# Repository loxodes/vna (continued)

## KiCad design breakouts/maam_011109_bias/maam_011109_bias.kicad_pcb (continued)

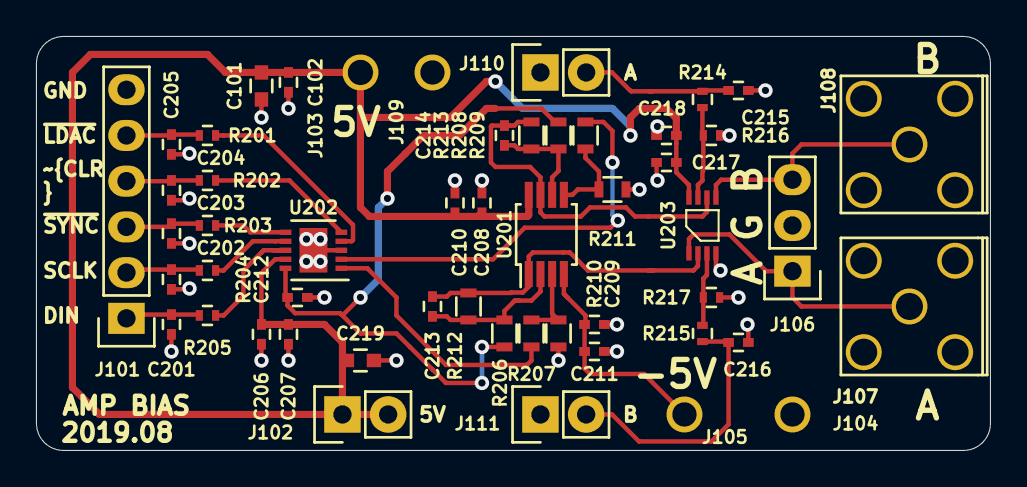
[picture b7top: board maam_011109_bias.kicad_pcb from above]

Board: 2 copper layers, 53.0 x 23.0 mm, 52 parts (0 on the bottom side), 28 nets.

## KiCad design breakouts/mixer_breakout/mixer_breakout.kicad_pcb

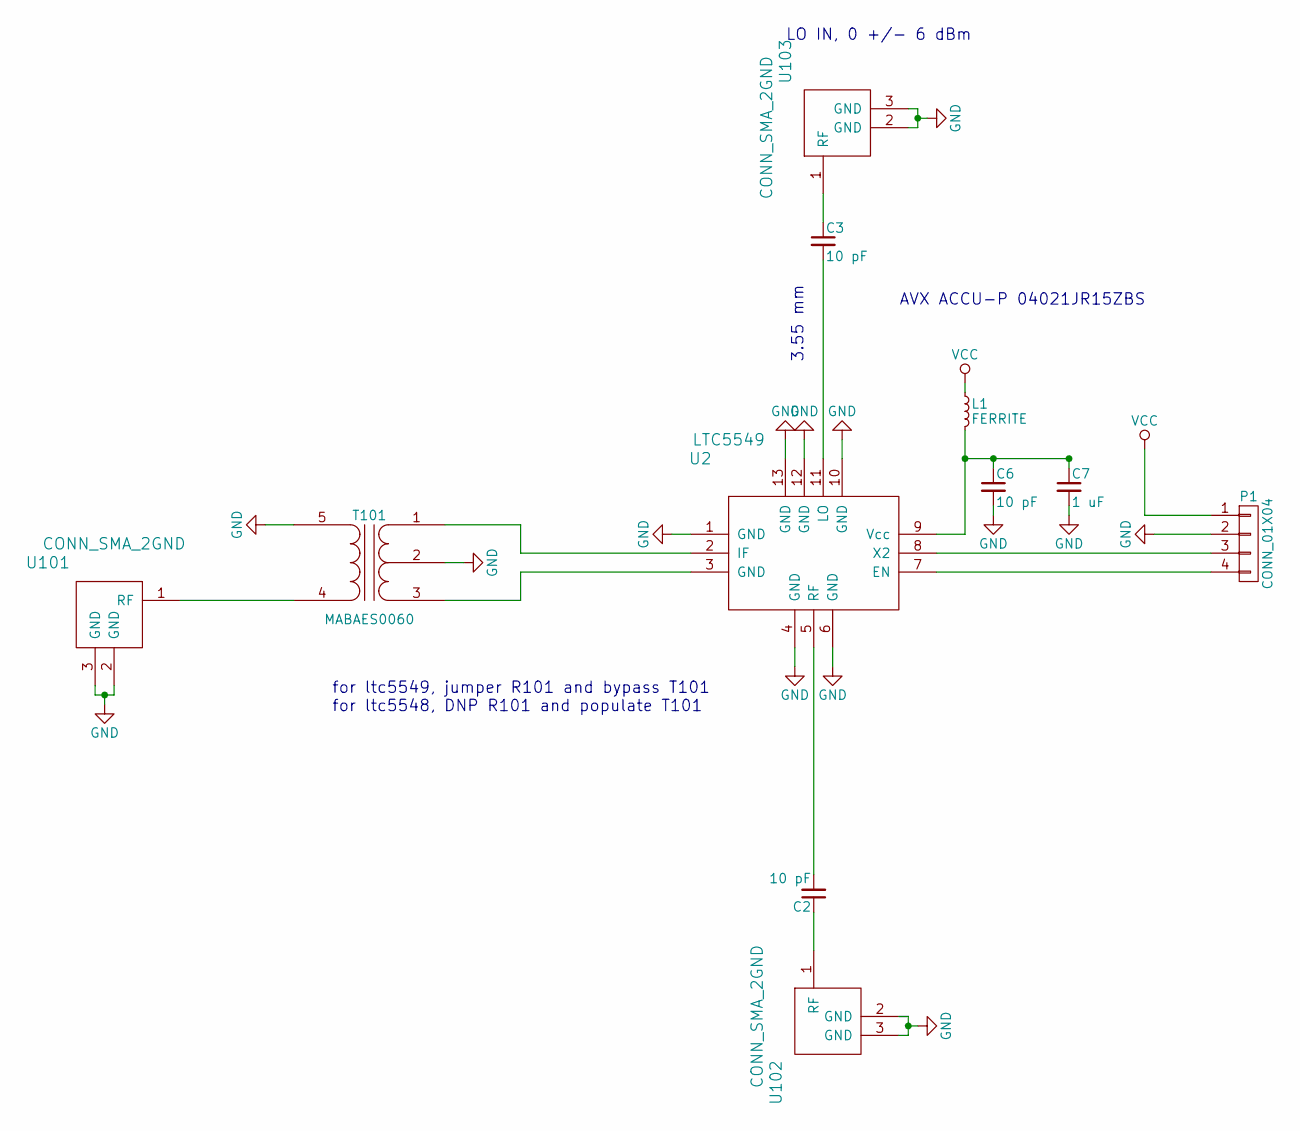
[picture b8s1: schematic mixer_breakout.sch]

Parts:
C2, C3: 10 pF; C_0402
C6: 10 pF; C_0603
C7: 1 uF; C_0603
L1: FERRITE; C_0603
P1: CONN_01X04; Pin_Header_Straight_1x04
T101: MABAES0060; 5LEAD_BALUN_4p83mm_3p3mm
U2: LTC5549; QFN_12_3mm2mm
U101, U102, U103: CONN_SMA_2GND; 142-0721-882_sma_cutout

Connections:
GND: C6.2, C7.2, P1.2, T101.2 (PM), T101.5 (S2), U2.1 (GND), U2.4 (GND), U2.6 (GND), U2.10 (GND), U2.12 (GND), U2.13 (GND), U101.2 (GND), U101.3 (GND), U102.2 (GND), U102.3 (GND), U103.2 (GND), U103.3 (GND)
unnamed: C2.1, U102.1 (RF)
unnamed: C2.2, U2.5 (RF)
unnamed: C3.1, U103.1 (RF)
unnamed: C3.2, U2.11 (LO)
unnamed: C6.1, C7.1, L1.2, U2.9 (Vcc)
unnamed: P1.3, U2.8 (X2)
unnamed: P1.4, U2.7 (EN)
unnamed: T101.3 (PR2), U2.3 (GND)
unnamed: T101.1 (PR1), U2.2 (IF)
unnamed: T101.4 (S1), U101.1 (RF)
VCC: L1.1, P1.1

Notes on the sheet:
3.55 mm
LO IN, 0 +/- 6 dBm
AVX ACCU-P 04021JR15ZBS
for ltc5549, jumper R101 and bypass T101 for ltc5548, DNP R101 and populate T101

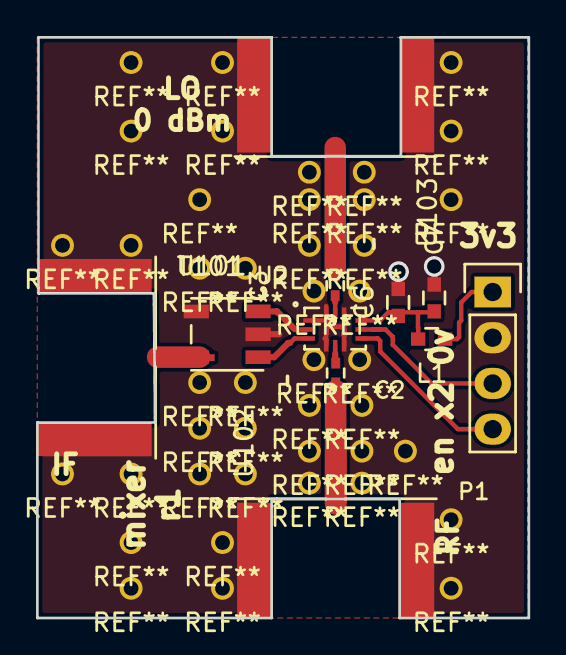
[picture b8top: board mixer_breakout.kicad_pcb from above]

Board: 4 copper layers, 27.3 x 32.3 mm, 11 parts (0 on the bottom side), 12 nets.
